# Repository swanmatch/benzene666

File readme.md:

# benzene666ビルドガイド

## 材料

### キットに含まれるもの

| 品目             | 数量 |
| ---------------- | ---- |
| PCB              | 2枚  |
| トッププレート   | 2枚  |
| ボトムプレート   | 2枚  |
| OLED保護プレート | 2枚  |
| ProMicro         | 2個  |
| ダイオード       | 56個 |
| LED              | 56個 |
| Kailhソケット    | 56個 |
| M24mmネジ        | 28本 |
| 7mm六角スペーサ  | 12本 |
| 8mm丸スペーサ    | 4本  |
| 低頭ネジ         | 4本  |
| ゴム足           | 10本 |

### キット以外で必要なもの
| 品目                  | 数量 |
| --------------------- | ---- |
| スイッチ              | 56個 |
| キーキャップ          | 56個 |
| TRRSまたはTRSケーブル | 1本  |
| USBケーブル           | 1本  |

### オプション品

| 品目       | 数量 |
| ---------- | ---- |
| コンスルー | 4本  |
| M6ボルト   | 6本  |
| M6ナット   | 6個  |
| *)OLED     | 2個  |

OLEDは動作未検証です。

## 組み立て手順

### LED

LEDをはんだ付けします。

シルクで白く囲ってあるのが一番大きいパッドです。

温度調整はんだごてで220度くらいに設定してください。もたついてると壊れます。

### ダイオード

ダイオードをはんだ付けしてください。向きに気をつけてください。

スルーホールの場合は黒が上、表面実装の場合うっすら線が書いてあるほうが上です。

### ソケット

ソケットをはんだ付けしてください。

### TRRS、リセットスイッチ

はんだ付けしてください。

### ProMicro

ここだけは間違えるとリカバリが面倒なので、細心の注意をして作業にあたってください。

コンスルーを使う場合はHelixなどのビルドガイドを参考にしてください。

四角く囲ってあるところに付属のピンを指して裏からはんだ付けして、表面にProMicroを指してはんだ付けしてください。

### スイッチ

トッププレートにスイッチをはめて、PCBに刺します。

このときすべてのピンが真っすぐになっていることを確認してください。

ピンが折れてしまいます。

### OLED保護プレート

PCB裏側から丸スペーサーをネジ止めして、表側に保護プレートを挟み込む形で低頭ネジでとめます。

### プレート

六角スペーサーとネジでPCBをサンドします。

ボトムプレートにゴム足を貼り付けてください。

反対側も同様に組み立てます。

### ファームウェア

```sh
git clone https://github.com/swanmatch/qmk_firmware.git
cd qmk_firmware
make benzene:swan:avrdude
```

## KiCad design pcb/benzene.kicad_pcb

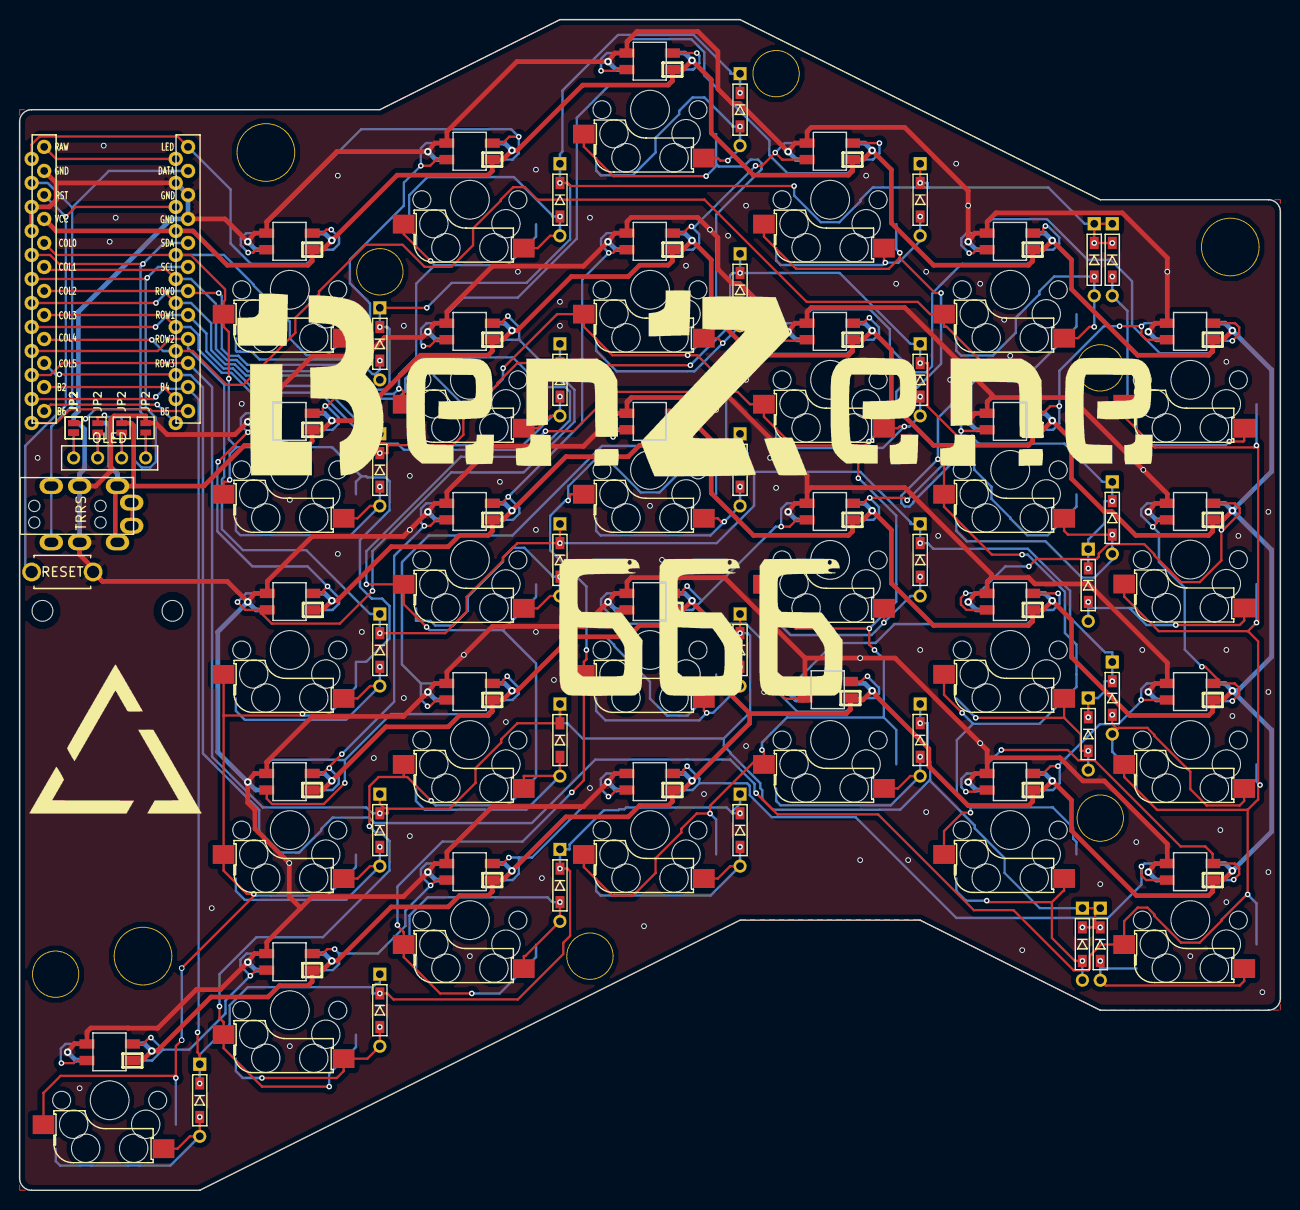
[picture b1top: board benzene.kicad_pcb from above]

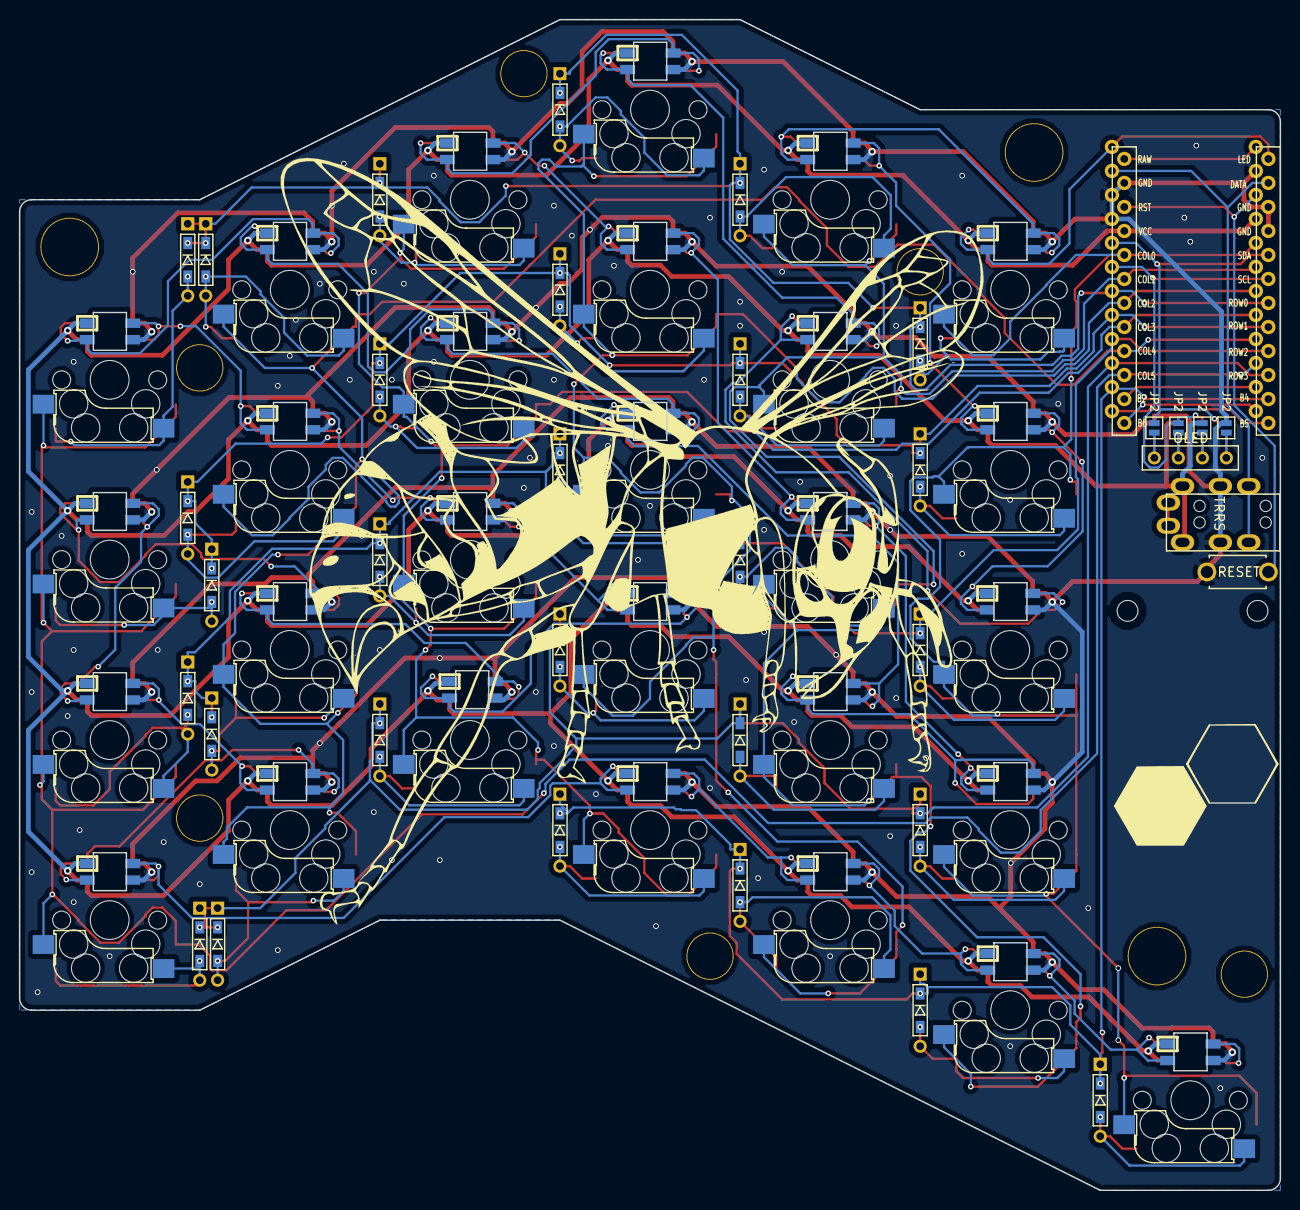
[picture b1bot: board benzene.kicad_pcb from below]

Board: 2 copper layers, 133.4 x 123.8 mm, 110 parts (6 on the bottom side), 77 nets.

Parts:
D1, D2, D3, D4, D5, D6, D7, D8, D9, D10, D11, D12, D13, D14, D15, D16, D17, D18, D19, D20, D21, D22, D23, D24, D25, D26, D27, D28: D; D3_TH_SMD
G1: LOGO; hxa_msk
G2: LOGO; hxa_slk
HOLE_M2_0, HOLE_M2_1: VAL**; HOLE_M2
J1: MJ-4PP-9
J2, J3, J4, J5, J6, J7, J8, J9, J10: JP2; Jumper
L1, L2, L3, L4, L5, L6, L7, L8, L9, L10, L11, L12, L13, L14, L15, L16, L17, L18, L19, L20, L21, L22, L23, L24, L25, L26, L27, L28: SK6812MINI; SK6812MINI_rev
OLED1: OLED
RESET1: SW_PUSH; ResetSW
Ref0, Ref1, Ref2, Ref3, Ref4, Ref5, Ref6, Ref7, Ref8: Val**; HOLE
SW1, SW2, SW3, SW4, SW5, SW6, SW7, SW8, SW9, SW10, SW11, SW12, SW13, SW14, SW15, SW16, SW17, SW18, SW19, SW20, SW21, SW22, SW23, SW24, SW25, SW26, SW27, SW28: SW_PUSH; CherryMX_Hotswap_outline
U1: ProMicro; ProMicro_v2

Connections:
DATA: J1.B, U1.2
GND: J1.C, J2.1, J10.1, L1.2, L2.2, L3.2, L4.2, L5.2, L6.2, L7.2, L8.2, L9.2, L10.2, L11.2, L12.2, L13.2, L14.2, L15.2, L16.2, L17.2, L18.2, L19.2, L20.2, L21.2, L22.2, L23.2, L24.2, L25.2, L26.2, L27.2, L28.2, RESET1.2, U1.3, U1.4, U1.23
LED: L1.3, U1.1
unnamed: D1.2, SW1.2
unnamed: D2.2, SW2.2
unnamed: D3.2, SW3.2
unnamed: D4.2, SW4.2
unnamed: D5.2, SW5.2
unnamed: D6.2, SW6.2
unnamed: D7.2, SW7.2
unnamed: D8.2, SW8.2
unnamed: D9.2, SW9.2
unnamed: D10.2, SW10.2
unnamed: D11.2, SW11.2
unnamed: D12.2, SW12.2
unnamed: D13.2, SW13.2
unnamed: D14.2, SW14.2
unnamed: D15.2, SW15.2
unnamed: D16.2, SW16.2
unnamed: D17.2, SW17.2
unnamed: D18.2, SW18.2
unnamed: D19.2, SW19.2
unnamed: D20.2, SW20.2
unnamed: D21.2, SW21.2
unnamed: D22.2, SW22.2
unnamed: D23.2, SW23.2
unnamed: D24.2, SW24.2
unnamed: D25.2, SW25.2
unnamed: D26.2, SW26.2
unnamed: D27.2, SW27.2
unnamed: D28.2, SW28.2
unnamed: J2.2, J7.2, OLED1.4
unnamed: J4.2, J8.2, OLED1.3
unnamed: J5.2, J9.2, OLED1.2
unnamed: J3.2, J6.2, J10.2, OLED1.1
unnamed: L1.1, L2.3
unnamed: L2.1, L7.3
unnamed: L3.1, L4.3
unnamed: L3.3, L8.1
unnamed: L4.1, L9.3
unnamed: L5.1, L6.3
unnamed: L5.3, L10.1
unnamed: L10.3, L15.1
unnamed: L11.1, L16.3
unnamed: L6.1, L11.3
unnamed: L12.1, L18.3
unnamed: L12.3, L17.1
unnamed: L8.3, L13.1
unnamed: L7.1, L13.3
unnamed: L14.1, L19.3
unnamed: L9.1, L14.3
unnamed: L15.3, L20.1
unnamed: L16.1, L21.3
unnamed: L17.3, L22.1
unnamed: L18.1, L23.3
unnamed: L19.1, L20.3
unnamed: L21.1, L22.3
unnamed: L23.1, L24.3
unnamed: L24.1, L28.3
unnamed: L25.3, L26.1
unnamed: L26.3, L27.1
unnamed: L27.3, L28.1
RST: RESET1.1, U1.22
SCL: J5.1, J8.1, U1.6
SDA: J3.1, J6.1, J7.1, U1.5
VCC: J1.D, J4.1, J9.1, L1.4, L2.4, L3.4, L4.4, L5.4, L6.4, L7.4, L8.4, L9.4, L10.4, L11.4, L12.4, L13.4, L14.4, L15.4, L16.4, L17.4, L18.4, L19.4, L20.4, L21.4, L22.4, L23.4, L24.4, L25.4, L26.4, L27.4, L28.4, U1.21
col0: SW1.1, SW7.1, SW13.1, SW19.1, SW25.1, U1.20
col1: SW2.1, SW8.1, SW14.1, SW20.1, SW26.1, U1.19
col2: SW3.1, SW9.1, SW15.1, SW21.1, SW27.1, U1.18
col3: SW4.1, SW10.1, SW16.1, SW22.1, SW28.1, U1.17
col4: SW5.1, SW11.1, SW17.1, SW23.1, U1.16
col5: SW6.1, SW12.1, SW18.1, SW24.1, U1.15
row0: D1.1, D2.1, D3.1, D4.1, D5.1, D6.1, U1.7
row1: D7.1, D8.1, D9.1, D10.1, D11.1, D12.1, U1.8
row2: D13.1, D14.1, D15.1, D16.1, D17.1, D18.1, U1.9
row3: D19.1, D20.1, D21.1, D22.1, D23.1, D24.1, U1.10
row4: D25.1, D26.1, D27.1, D28.1, U1.11

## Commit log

2019-11-12 Set theme jekyll-theme-hacker
